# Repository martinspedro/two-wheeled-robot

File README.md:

# E4 Project 
Project for the curricular unit Eletrónica IV (E4)

## Objectives
The proposed project consists on a small two wheel robot.

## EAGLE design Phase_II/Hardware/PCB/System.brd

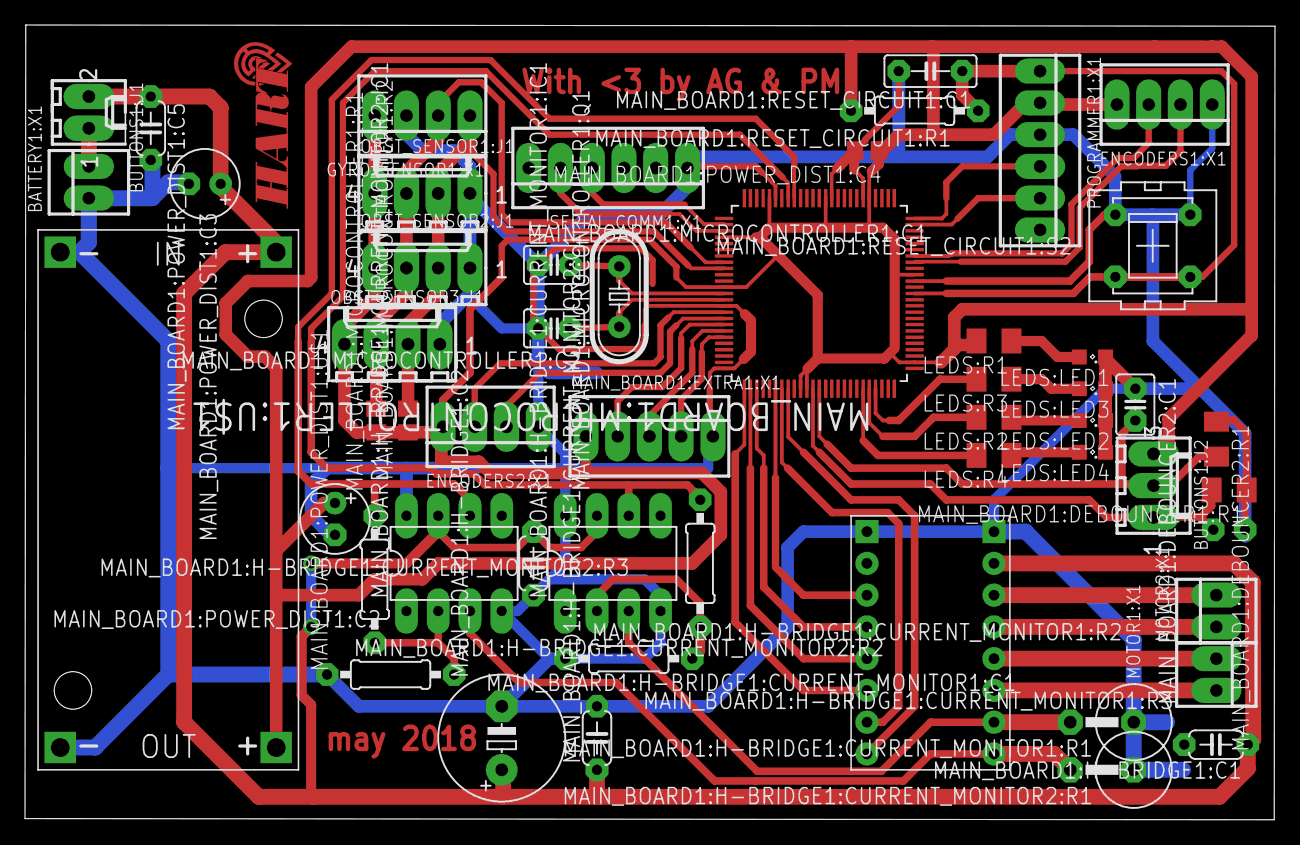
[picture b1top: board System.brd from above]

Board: 2 copper layers, 100.0 x 63.6 mm, 53 parts (1 on the bottom side), 45 nets.

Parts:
BATTERY1:X1: 22-23-2021
BUTTONS1:J1: 22-27-2021-02; 6410-02
BUTTONS1:J2: 22-27-2031-03; 6410-03
ENCODERS1:X1, ENCODERS2:X1: 22-23-2041
GYRO_SENSOR1:X1: 22-23-2041
LEDS:LED1, LEDS:LED2, LEDS:LED3, LEDS:LED4: SML0805
LEDS:R1, LEDS:R2, LEDS:R3, LEDS:R4: M1206
MAIN_BOARD1:DEBOUNCER1:C1, MAIN_BOARD1:DEBOUNCER2:C1: C025-030X050
MAIN_BOARD1:DEBOUNCER1:R1, MAIN_BOARD1:DEBOUNCER2:R1: M1206
MAIN_BOARD1:EXTRA1:X1: 22-23-2051
MAIN_BOARD1:H-BRIDGE1:C1, MAIN_BOARD1:POWER_DIST1:C5: 100p; C050-024X044
MAIN_BOARD1:H-BRIDGE1:C2: 10u; E5-10,5
MAIN_BOARD1:H-BRIDGE1:CURRENT_MONITOR1:C1, MAIN_BOARD1:H-BRIDGE1:CURRENT_MONITOR2:C1: 100nf; C050-024X044
MAIN_BOARD1:H-BRIDGE1:CURRENT_MONITOR1:IC1, MAIN_BOARD1:H-BRIDGE1:CURRENT_MONITOR2:IC1: MAX406CPA; DIL08
MAIN_BOARD1:H-BRIDGE1:CURRENT_MONITOR1:R1, MAIN_BOARD1:H-BRIDGE1:CURRENT_MONITOR2:R1: 0617V
MAIN_BOARD1:H-BRIDGE1:CURRENT_MONITOR1:R2, MAIN_BOARD1:H-BRIDGE1:CURRENT_MONITOR1:R3, MAIN_BOARD1:H-BRIDGE1:CURRENT_MONITOR2:R2, MAIN_BOARD1:H-BRIDGE1:CURRENT_MONITOR2:R3: 0207/10
MAIN_BOARD1:H-BRIDGE1:U$1: DRV8833_MODULE
MAIN_BOARD1:MICROCONTROLLER1:C1, MAIN_BOARD1:MICROCONTROLLER1:C2: 20p; C025-030X050
MAIN_BOARD1:MICROCONTROLLER1:Q1: 8M; HC49/S
MAIN_BOARD1:MICROCONTROLLER1:R1, MAIN_BOARD1:MICROCONTROLLER1:R2: M0805
MAIN_BOARD1:MICROCONTROLLER1:U$1: PIC32MX795F512L-80I/PF; QFP50P1600X1600X120-100N
MAIN_BOARD1:POWER_DIST1:C2, MAIN_BOARD1:POWER_DIST1:C3: 10u; E2,5-6
MAIN_BOARD1:POWER_DIST1:C4: 100p; C0805
MAIN_BOARD1:POWER_DIST1:U$1: DC-DC-STEP-DOWN-LM2596
MAIN_BOARD1:RESET_CIRCUIT1:C1: 100n; C050-025X075
MAIN_BOARD1:RESET_CIRCUIT1:R1: 10k; 0207/10
MAIN_BOARD1:RESET_CIRCUIT1:S2: PVA1R
MOTOR1:X1, MOTOR2:X1: 22-23-2021
OBST_SENSOR1:J1, OBST_SENSOR2:J1, OBST_SENSOR3:J1: 22-27-2041-04; 6410-04
PROGRAMMER1:X1: 22-23-2061
SERIAL_COMM1:X1: 22-23-2061

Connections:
+3V3: BUTTONS1:J2.3, ENCODERS1:X1.4, ENCODERS2:X1.4, GYRO_SENSOR1:X1.4, LEDS:R1.2, MAIN_BOARD1:EXTRA1:X1.1, MAIN_BOARD1:MICROCONTROLLER1:R1.1, MAIN_BOARD1:MICROCONTROLLER1:R2.1, MAIN_BOARD1:MICROCONTROLLER1:U$1.2, MAIN_BOARD1:MICROCONTROLLER1:U$1.16, MAIN_BOARD1:MICROCONTROLLER1:U$1.30, MAIN_BOARD1:MICROCONTROLLER1:U$1.37, MAIN_BOARD1:MICROCONTROLLER1:U$1.46, MAIN_BOARD1:MICROCONTROLLER1:U$1.54, MAIN_BOARD1:MICROCONTROLLER1:U$1.62, MAIN_BOARD1:MICROCONTROLLER1:U$1.85, MAIN_BOARD1:MICROCONTROLLER1:U$1.86, MAIN_BOARD1:POWER_DIST1:C2.+, MAIN_BOARD1:POWER_DIST1:C4.1, MAIN_BOARD1:POWER_DIST1:U$1.OUT+, MAIN_BOARD1:RESET_CIRCUIT1:R1.2, OBST_SENSOR1:J1.4, OBST_SENSOR2:J1.4, OBST_SENSOR3:J1.4, PROGRAMMER1:X1.2
GND: BATTERY1:X1.1, ENCODERS1:X1.1, ENCODERS2:X1.1, GYRO_SENSOR1:X1.3, LEDS:LED1.C, LEDS:LED2.C, LEDS:LED3.C, LEDS:LED4.C, MAIN_BOARD1:DEBOUNCER1:C1.1, MAIN_BOARD1:DEBOUNCER1:R1.1, MAIN_BOARD1:DEBOUNCER2:C1.1, MAIN_BOARD1:DEBOUNCER2:R1.1, MAIN_BOARD1:EXTRA1:X1.5, MAIN_BOARD1:H-BRIDGE1:C1.2, MAIN_BOARD1:H-BRIDGE1:C2.-, MAIN_BOARD1:H-BRIDGE1:CURRENT_MONITOR1: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.2, MAIN_BOARD1:H-BRIDGE1:CURRENT_MONITOR1: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.4, MAIN_BOARD1:H-BRIDGE1:CURRENT_MONITOR1: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.8, MAIN_BOARD1:H-BRIDGE1:CURRENT_MONITOR1: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.1, MAIN_BOARD1:H-BRIDGE1:CURRENT_MONITOR1: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.1, MAIN_BOARD1:H-BRIDGE1:CURRENT_MONITOR2: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.2, MAIN_BOARD1:H-BRIDGE1:CURRENT_MONITOR2: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.4, MAIN_BOARD1:H-BRIDGE1:CURRENT_MONITOR2: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.8, MAIN_BOARD1:H-BRIDGE1:CURRENT_MONITOR2: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.1, MAIN_BOARD1:H-BRIDGE1:CURRENT_MONITOR2: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.1, MAIN_BOARD1:H-BRIDGE1:U$1.GND, MAIN_BOARD1:H-BRIDGE1:U$1.GND2, MAIN_BOARD1:MICROCONTROLLER1:C1.1, MAIN_BOARD1:MICROCONTROLLER1:C2.2, MAIN_BOARD1:MICROCONTROLLER1:U$1.15, MAIN_BOARD1:MICROCONTROLLER1:U$1.31, MAIN_BOARD1:MICROCONTROLLER1:U$1.36, MAIN_BOARD1:MICROCONTROLLER1:U$1.45, MAIN_BOARD1:MICROCONTROLLER1:U$1.65, MAIN_BOARD1:MICROCONTROLLER1:U$1.75, MAIN_BOARD1:POWER_DIST1:C2.-, MAIN_BOARD1:POWER_DIST1:C3.-, MAIN_BOARD1:POWER_DIST1:C4.2, MAIN_BOARD1:POWER_DIST1:C5.2, MAIN_BOARD1:POWER_DIST1:U$1.IN-, MAIN_BOARD1:POWER_DIST1:U$1.OUT-, MAIN_BOARD1:RESET_CIRCUIT1:C1.2, MAIN_BOARD1:RESET_CIRCUIT1:S2.2, MAIN_BOARD1:RESET_CIRCUIT1:S2.4, OBST_SENSOR1:J1.1, OBST_SENSOR2:J1.1, OBST_SENSOR3:J1.1, PROGRAMMER1:X1.3, SERIAL_COMM1:X1.1
LEDS:N$1: LEDS:LED4.A, LEDS:R4.1
LEDS:N$2: LEDS:LED3.A, LEDS:R3.1
LEDS:N$3: LEDS:LED2.A, LEDS:R2.1
LEDS:N$4: LEDS:LED1.A, LEDS:R1.1
MAIN_BOARD1:H-BRIDGE1:CURRENT_MONITOR1:N$1: MAIN_BOARD1:H-BRIDGE1:CURRENT_MONITOR1: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.2, MAIN_BOARD1:H-BRIDGE1:CURRENT_MONITOR1: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.2, MAIN_BOARD1:H-BRIDGE1:CURRENT_MONITOR1: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.2
MAIN_BOARD1:H-BRIDGE1:CURRENT_MONITOR2:N$1: MAIN_BOARD1:H-BRIDGE1:CURRENT_MONITOR2: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.2, MAIN_BOARD1:H-BRIDGE1:CURRENT_MONITOR2: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.2, MAIN_BOARD1:H-BRIDGE1:CURRENT_MONITOR2: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.2
MAIN_BOARD1:H-BRIDGE1:N$8: MAIN_BOARD1:H-BRIDGE1:CURRENT_MONITOR2: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.3, MAIN_BOARD1:H-BRIDGE1:CURRENT_MONITOR2: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.2, MAIN_BOARD1:H-BRIDGE1:U$1.BISEN
MAIN_BOARD1:H-BRIDGE1:N$9: MAIN_BOARD1:H-BRIDGE1:CURRENT_MONITOR1: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.3, MAIN_BOARD1:H-BRIDGE1:CURRENT_MONITOR1: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.2, MAIN_BOARD1:H-BRIDGE1:U$1.AISEN
MAIN_BOARD1:MICROCONTROLLER1:N$4: MAIN_BOARD1:MICROCONTROLLER1:C1.2, MAIN_BOARD1:MICROCONTROLLER1:Q1.2, MAIN_BOARD1:MICROCONTROLLER1:U$1.63
MAIN_BOARD1:MICROCONTROLLER1:N$6: MAIN_BOARD1:MICROCONTROLLER1:C2.1, MAIN_BOARD1:MICROCONTROLLER1:Q1.1, MAIN_BOARD1:MICROCONTROLLER1:U$1.64
MAIN_BOARD1:N$1: MAIN_BOARD1:H-BRIDGE1:U$1.AIN1, MAIN_BOARD1:MICROCONTROLLER1:U$1.76
MAIN_BOARD1:N$2: MAIN_BOARD1:H-BRIDGE1:U$1.AIN2, MAIN_BOARD1:MICROCONTROLLER1:U$1.77
MAIN_BOARD1:N$3: MAIN_BOARD1:H-BRIDGE1:U$1.BIN1, MAIN_BOARD1:MICROCONTROLLER1:U$1.81
MAIN_BOARD1:N$4: MAIN_BOARD1:H-BRIDGE1:U$1.BIN2, MAIN_BOARD1:MICROCONTROLLER1:U$1.78
MAIN_BOARD1:N$5: MAIN_BOARD1:H-BRIDGE1:CURRENT_MONITOR2: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.6, MAIN_BOARD1:H-BRIDGE1:CURRENT_MONITOR2: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.1, MAIN_BOARD1:MICROCONTROLLER1:U$1.42
MAIN_BOARD1:N$6: MAIN_BOARD1:H-BRIDGE1:CURRENT_MONITOR1: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.6, MAIN_BOARD1:H-BRIDGE1:CURRENT_MONITOR1: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.1, MAIN_BOARD1:MICROCONTROLLER1:U$1.43
MAIN_BOARD1:N$7: MAIN_BOARD1:EXTRA1:X1.2, MAIN_BOARD1:MICROCONTROLLER1:U$1.68
MAIN_BOARD1:N$8: MAIN_BOARD1:EXTRA1:X1.3, MAIN_BOARD1:MICROCONTROLLER1:U$1.69
MAIN_BOARD1:N$9: MAIN_BOARD1:EXTRA1:X1.4, MAIN_BOARD1:MICROCONTROLLER1:U$1.70
MAIN_BOARD1:N$12: MAIN_BOARD1:H-BRIDGE1:U$1.NFAULT, MAIN_BOARD1:MICROCONTROLLER1:U$1.83
MAIN_BOARD1:N$13: MAIN_BOARD1:H-BRIDGE1:U$1.NSLEEP, MAIN_BOARD1:MICROCONTROLLER1:U$1.82
unnamed: GYRO_SENSOR1:X1.2, MAIN_BOARD1:MICROCONTROLLER1:R1.2, MAIN_BOARD1:MICROCONTROLLER1:U$1.58, OBST_SENSOR1:J1.3, OBST_SENSOR2:J1.3, OBST_SENSOR3:J1.3
unnamed: GYRO_SENSOR1:X1.1, MAIN_BOARD1:MICROCONTROLLER1:R2.2, MAIN_BOARD1:MICROCONTROLLER1:U$1.59, OBST_SENSOR1:J1.2, OBST_SENSOR2:J1.2, OBST_SENSOR3:J1.2
unnamed: MAIN_BOARD1:MICROCONTROLLER1:U$1.52, SERIAL_COMM1:X1.4
unnamed: MAIN_BOARD1:MICROCONTROLLER1:U$1.53, SERIAL_COMM1:X1.5
unnamed: BATTERY1:X1.2, BUTTONS1:J1.1
unnamed: MAIN_BOARD1:H-BRIDGE1:U$1.AOUT1, MOTOR1:X1.2
unnamed: MAIN_BOARD1:H-BRIDGE1:U$1.AOUT2, MOTOR1:X1.1
unnamed: MAIN_BOARD1:H-BRIDGE1:U$1.BOUT1, MOTOR2:X1.2
unnamed: MAIN_BOARD1:H-BRIDGE1:U$1.BOUT2, MOTOR2:X1.1
unnamed: ENCODERS1:X1.3, MAIN_BOARD1:MICROCONTROLLER1:U$1.19
unnamed: ENCODERS1:X1.2, MAIN_BOARD1:MICROCONTROLLER1:U$1.18
unnamed: BUTTONS1:J2.1, MAIN_BOARD1:DEBOUNCER1:C1.2, MAIN_BOARD1:DEBOUNCER1:R1.2, MAIN_BOARD1:MICROCONTROLLER1:U$1.87
unnamed: BUTTONS1:J2.2, MAIN_BOARD1:DEBOUNCER2:C1.2, MAIN_BOARD1:DEBOUNCER2:R1.2, MAIN_BOARD1:MICROCONTROLLER1:U$1.88
unnamed: MAIN_BOARD1:MICROCONTROLLER1:U$1.24, PROGRAMMER1:X1.5
unnamed: MAIN_BOARD1:MICROCONTROLLER1:U$1.25, PROGRAMMER1:X1.4
unnamed: ENCODERS2:X1.3, MAIN_BOARD1:MICROCONTROLLER1:U$1.66
unnamed: LEDS:R4.2, MAIN_BOARD1:MICROCONTROLLER1:U$1.95
unnamed: LEDS:R3.2, MAIN_BOARD1:MICROCONTROLLER1:U$1.97
unnamed: LEDS:R2.2, MAIN_BOARD1:MICROCONTROLLER1:U$1.96
unnamed: ENCODERS2:X1.2, MAIN_BOARD1:MICROCONTROLLER1:U$1.67
unnamed: MAIN_BOARD1:MICROCONTROLLER1:U$1.13, MAIN_BOARD1:RESET_CIRCUIT1:C1.1, MAIN_BOARD1:RESET_CIRCUIT1:R1.1, MAIN_BOARD1:RESET_CIRCUIT1:S2.1, MAIN_BOARD1:RESET_CIRCUIT1:S2.3, PROGRAMMER1:X1.1
VCC: BUTTONS1:J1.2, MAIN_BOARD1:H-BRIDGE1:C1.1, MAIN_BOARD1:H-BRIDGE1:C2.+, MAIN_BOARD1:H-BRIDGE1:CURRENT_MONITOR1: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.1, MAIN_BOARD1:H-BRIDGE1:CURRENT_MONITOR1: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.7, MAIN_BOARD1:H-BRIDGE1:CURRENT_MONITOR2: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.1, MAIN_BOARD1:H-BRIDGE1:CURRENT_MONITOR2: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.7, MAIN_BOARD1:H-BRIDGE1:U$1.VIN, MAIN_BOARD1:POWER_DIST1:C3.+, MAIN_BOARD1:POWER_DIST1:C5.1, MAIN_BOARD1:POWER_DIST1:U$1.IN+

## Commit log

2018-02-19 [WIP] Incomplete version of the project proposal document
2018-02-19 [WIP] Corrected some types. Added PDF
2018-02-19 Added diagrams for level 0 and 1
2018-02-19 [WIP] Fixed more typos
2018-02-19 [WIP] Update repo
2018-02-19 Increased dpi of images
2018-02-19 Added instrumentation diagrams
2018-02-19 Simplified the diagrams, redone the robot up view
2018-02-20 Added material list
2018-02-20 [WIP] Proposal v0.2
2018-02-20 [UPDATE] New version of Proposal
2018-02-20 Added control section
2018-02-20 Added figures
2018-02-20 Update images
2018-02-20 [WIP] Cadeias de Instrumentação introduzidas
2018-02-20 [WIP] Updated Markdown and header file
2018-02-20 [UPDATE] Removed auxiliary files | Update metadata files
2018-02-20 [DONE] Final Version of Project Proposal
2018-02-20 Changes to up view in classes
2018-02-23 [DOC] Added Reference Documentation
    PIC Datasheets, Reference Notes for level shifting and chipKIT
2018-02-27 [MATERIAL] Add DETI components list
2018-02-27 [PIC] Added chipkit board PIC32MX Schematic
2018-03-04 Changes in level 0 diagram
2018-03-05 Added phase 1 folder
2018-03-05 Material excel
2018-03-06 Added PERT diagram, needs checking
2018-03-06 Added some instrumentation chains
2018-03-06 Added PERT diagram
2018-03-06 Exported most chains, i2c, button, current, added visio files for encoder chain
2018-03-06 Change in level 0 diagram
2018-03-06 PERT update
2018-03-20 [WIP] Added configuration bits for PIC32MX
2018-03-26 [WIP] UART device driver first version
2018-04-03 [CONFIG] Update configuration bits
    Added gitignore
2018-04-03 [DONE] UART by polling
2018-04-03 Added Lista de Material
2018-04-08 [PWM] First version of PWM module completed
2018-04-12 Added initial renders for robot structure
2018-04-24 [DATASHEETS] Removed datasheets from repo
2018-04-24 Add sendchar header to uart1.h
2018-04-24 First ADC version working in manual mode
2018-04-24 [ADC] Add integration with UART and send debug characters
2018-04-24 Add PWM makefile
2018-04-25 Added print and read integer functions to UART
2018-04-25 Added gitignore
2018-04-25 ADC reads Analog pin and prints voltage using UART1
2018-04-28 [ADC] Updated ADC doxygen documentation
2018-05-01 First Operational version of Interrupt on change pin
2018-05-01 Improve documentation on global.h
2018-05-01 Update documentation on Interrupts and encoder
2018-05-01 Init Device Driver for encoder
    Implemented for Left motor
2018-05-03 Added support for quadrature encoder
    Added ifdef in order to use chipkit and PIC direct pins
2018-05-04 Working version of I2C2 module witout interruptions
2018-05-05 Separate Global Interrupt file from Encoder project
2018-05-05 Update project wide header files
2018-05-05 Small changes on interrupts file
2018-05-05 Update State Machine Quadrature Encoder
2018-05-05 Update main to perform some debug
2018-05-06 [PWM] Extend basic PWM module Implementation to 4 PWM
    Also:
    - Create Global PWM module
    - Create a module for each PWM
    - Created module for Timer 2r
    - Improved Documentation for all modules
    - Updated main.c to test all PWM simultaneously
2018-05-06 Updated gitignore and DEVCPGx configuration bits
2018-05-06 Initial Work on DRV8833 - h-bridge motor driver
2018-05-07 [ENCODER] Expanded to both motors. Uses LUT
2018-05-07 Moved priority defines from header to c file
2018-05-07 Implemented ADC using Interrupts
    Not working in the desired timings
2018-05-08 VLP sensor working without interrupts
2018-05-08 Added MPU dev driver
2018-05-08 [CLEANUP] - removed vlx
2018-05-08 [CLEANUP] - I2C files
2018-05-08 Moved I2C project to phase II
2018-05-12 Improved UART DOcumentation, improved teste file and add more macros
2018-05-12 [NOT WORKING] UART using Circular buffer
2018-05-12 UART using interrupts
    Still buggy
2018-05-12 Added renders and schematics of robot
2018-05-12 Move MPU.X project to PhaseII
2018-05-12 Added I2C project doxygen comments
2018-05-12 MPU includes from other folders
2018-05-12 [UART] Final functional version
    puts and gets char, uint8
    puts strings, uint16
2018-05-12 Fixed samml typos in UART 1 device driver
2018-05-12 Started to implemente state machine for i2c interrupt
2018-05-13 Update Material List and organize
2018-05-13 Add dxf and stl to base folder
2018-05-13 [I2C] Added writeBytes and readBytes abstraction
2018-05-13 [MPU] Added function to get individual measurements & change to new abstraction layer from i2c
2018-05-13 [MPU] Test in main using uart to print data( need to calibrate delay)
2018-05-13 LIvro.xlsl commit due to pull
2018-05-13 [VLX] updated to new i2c abstraction and rearranjed the test
2018-05-13 [I2C] Added functions to handle bit writing
2018-05-13 [MPU] Working test, added function to init and bit handling
2018-05-13 [VLX] Test working
2018-05-14 [VLX] Change to tests in main, define for new adress setting
2018-05-14 [VLX] Swapped tofInit for sensorInit, remove unnecessary comments, added setAdress function
2018-05-14 [VLX] Delete old outdated files
2018-05-14 [I2C] Added write/read Bit, write/read Bits, write/read Byte, added DOXYGEN stuff
2018-05-14 [MPU] Added macros for separate test to ACC, GYRO and TEMP
2018-05-14 [MPU] Registers macro from .h to .c, changes in initMPU, added get/set OFFSETs to ACC and GYRO axis
2018-05-14 [Hardware] Update of the render(resizes), added picture of deti_pcb
2018-05-15 Improved UART test script
    Move flush to the configuration function
2018-05-15 [I2C] Adde i2c_ping and NACK error detection
2018-05-15 [I2C]Added clearI2CBuffer
2018-05-15 [I2C] Added ping_i2c as demo for i2c dev. driver, using clearBufferI2C
2018-05-15 [I2C] Remove old UART
2018-05-15 [PCB] Added final PCB desgin
2018-05-15 [I2C] Removed mpLab folders
2018-05-15 Set debug flag for encoder
2018-05-15 DRV8833 can control the motor operation and enable/disable the module
2018-05-15 ADC implemented with interruptions
    bug: interrupt to often
2018-05-15 Remove all files dont need to be in the repository
2018-05-17 Removed Phase I binary files
2018-05-17 Removed binary files from Phase II folder
2018-05-17 Updated gitignore to prevent undesired folders to be added
2018-05-21 [VLX] Added main(prob. ) filters before cleanup
2018-05-28 Add timer3 configuration files
2018-05-28 Add ADC version using Timer 3 - buggy
2018-05-28 FIxed bug that enabled instad of desabling the TIMER2 before initialization
2018-05-28 Last ADC version
2018-05-29 ADD communication protocol
2018-05-29 Add Timer 4 implementation
2018-05-29 Add error verification to UART get_uint8
2018-05-29 Add critical sections to encoders mplementation
    New function to reset encoder state
    macros for enabling/disabling all encoders
2018-05-29 Add routine to detect fault conditions
2018-05-29 Select Internal Oscillator in pragma configuration
2018-05-30 Added PWM5 device driver
2018-05-30 Updated DRV8833 to use PWM peripherals from PCb
2018-05-30 Updated Encoder to include Debug with UART
2018-05-30 Add physical contraints and robot dimensions
2018-05-30 Changes before I2C by interrupts
2018-05-30 Update PWM frequency to 2KHz
2018-05-30 Encoders coutner are public to other modules
2018-05-30 Fixed minor bugs on movement
    Added Weak pull up to nFault
    function headears for movement function made public
2018-05-30 Change comment to reflect manual alteration in pragma
2018-05-30 Minor adjustments
2018-05-30 First robot working version
    Moves forward, backwards, rotates CW & CCW.
    Emergency stop implemented
2018-05-30 VLX integration
2018-05-30 Added interrupt init to timer4
2018-05-30 Changed VLX intit sequence to reflect Sensors positioning
2018-05-30 Working version with distance detection
2018-06-03 Code state at presentation: 30 May
2018-06-03 Create class for IO pin mapping
2018-06-03 Improve documentation
2018-06-03 Updated Encoder Documentation
2018-06-03 Communication Protocol DOcumented
2018-06-03 Update DRV8833
2018-06-03 Full Encoder Module Documentation
2018-06-03 Full Documented interuptions module
2018-06-03 PWM modules full documentation
2018-06-03 Improved Timer 2 Documentation and Modularity
2018-06-03 Impoved Timer 3 Documentation and Modularity
2018-06-03 Improved Timer4 documentation and modularity
2018-06-03 Documentation added
2018-06-03 Removed Report folder from Doxygen search
2018-06-03 Improved modularity, documentation and code organization for robot module
2018-06-03 Improved Main with documentation
2018-06-03 Add nbproject folders to improve modularity
2018-06-03 Add reference to JLA in PID routine
2018-06-04 Presentation code version
2018-06-05 Add DRV8833 slow decay robot control functions
2018-06-05 Update ADC nbproject
2018-06-06 Activated START button
2018-06-06 Change initialization and measurement code from tof to robot module
2018-06-07 Add nbproject
2018-06-07 Add Phase III folder to gitignore

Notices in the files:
parts and their libraries:
diy-modules: Released under the Creative Commons Attribution 4.0 International License: http://creativecommons.org/licenses/by/4.0
